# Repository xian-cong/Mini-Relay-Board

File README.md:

# Mini Relay Board
### Functions
This relay board is designed to be as small as possible using KiCAD to perform functions:
```
  1. Relay Switch Function (250VAC/30VDC rated voltage, 3A-5A rated current)
  2. Power Supply (5V, up to 2A) for microcontroller (e.g. Jetson Nano, Raspberry Pi, Arduino...)
  3. Push Button Input with Kill Function (i.e. IC kills the power if push button is pressed ~20secs)
  4. General Output pin (3.3V, up to 10mA) for LED/indicators
  5. SMD LED Indicator for Relay
  ```
  
### Components
Components & Datasheets can be found [here](https://github.com/xian-cong/mini-relay-board/blob/main/Components%20%26%20Datasheet.txt).

### Board Schematic

### Board Layout

### 3D View of Board
**Top View** <br />
 <br />
**Isometric View** <br />

### Deployment View of Board

### Board without Components

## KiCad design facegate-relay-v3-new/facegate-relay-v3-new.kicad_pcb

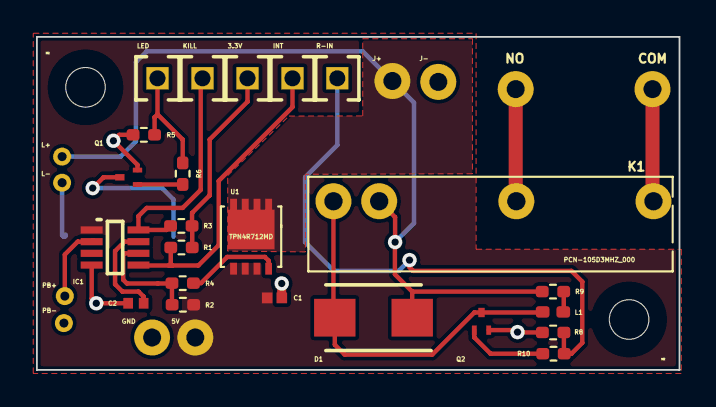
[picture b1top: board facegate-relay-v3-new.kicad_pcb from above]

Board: 2 copper layers, 35.7 x 18.5 mm, 35 parts (1 on the bottom side), 20 nets.

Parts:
3.3V: 3.3V; SAMTEC_MTMM-101-06-S-S-200
5V: 5V VIN; SAMTEC_MTMM-101-06-S-S-200
C1: 0.1μF; CAPC1005X55N
C2: 3μF; CAPC1005X55N
D1: SS34B; DIOM5336X320N
GND: GND; SAMTEC_MTMM-101-06-S-S-200
IC1: LTC2954; SOT65P280X100-8N
INT: GPIO; SAMTEC_MTMM-101-06-S-S-200
J+: Jetson Nano VIN; SAMTEC_MTMM-101-06-S-S-200
J-: GND; SAMTEC_MTMM-101-06-S-S-200
K1: PCN-105D3MHZ_000
KILL: GPIO; SAMTEC_MTMM-101-06-S-S-200
L1: LED; LED_0402_1005Metric_Pad0.77x0.64mm_HandSolder
L+: 5V LED; SAMTEC_MTMM-101-06-S-S-200
L-: GND LED; SAMTEC_MTMM-101-06-S-S-200
LED: GPIO; SAMTEC_MTMM-101-06-S-S-200
M2, M2#2: MountingHole_2.2mm_M2
NO: COM; ED120&slash_2DS
PB+: Push Button; SAMTEC_MTMM-101-06-S-S-200
PB-: Push Button GND; SAMTEC_MTMM-101-06-S-S-200
Q1: NTK3134NT1G
Q2: NTK3134NT; NTK3134NT1G
R1, R3, R5, R8: 10K; R_0402_1005Metric_Pad0.72x0.64mm_HandSolder
R2, R4: 100K; R_0402_1005Metric_Pad0.72x0.64mm_HandSolder
R6, R9, R10: 1K; R_0402_1005Metric_Pad0.72x0.64mm_HandSolder
R7: 5.1; R_2512_6332Metric_Pad1.40x3.35mm_HandSolder
R-IN: INPUT; SAMTEC_MTMM-101-06-S-S-200
U1: TPN4R712MD

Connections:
Earth: C1.1, C2.2, GND.01, IC1.4 (GND), J-.01, PB-.01, Q1.2, Q2.2, R5.2, R8.2
unnamed: 5V.01, C1.2, IC1.1 (VIN), R2.1, U1.1 (SOURCE), U1.2 (SOURCE), U1.3 (SOURCE)
unnamed: C2.1, IC1.7 (PDT)
unnamed: D1.1, J+.01, K1.2, L+.01, R9.1, U1.5 (DRAIN), U1.6 (DRAIN), U1.7 (DRAIN), U1.8 (DRAIN), U1.9 (DRAIN)
unnamed: D1.2, K1.1, L1.1 (K), Q2.3
unnamed: IC1.2 (~PB), PB+.01
unnamed: IC1.5 (~INT), INT.01, R1.1
unnamed: IC1.6 (EN/~EN), R2.2, R4.1
unnamed: IC1.8 (~KILL), KILL.01, R3.1
unnamed: 3.3V.01, R1.2, R3.2
unnamed: LED.01, R5.1, R6.1
unnamed: L-.01, R7.1
unnamed: R8.1, R10.1, R-IN.01
unnamed: K1.4, NO.1
unnamed: K1.3, NO.2
unnamed: L1.2 (A), R9.2
unnamed: Q1.1, R6.2
unnamed: Q1.3, R7.2
unnamed: Q2.1, R10.2
unnamed: R4.2, U1.4 (GATE)
